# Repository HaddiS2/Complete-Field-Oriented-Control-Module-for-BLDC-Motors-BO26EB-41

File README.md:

# Complete-Field-Oriented-Control-Module-for-BLDC-Motors-BO26EB-41
Custom field-oriented control (FOC) motor controller with USB-C Power Delivery.

This repository contains the hardware design files, firmware, and test rig for a custom brushless motor controller built around field-oriented control (FOC). The board negotiates its supply voltage over USB-C Power Delivery using an STUSB4500, and measures rotor position with a TLE5009 magnetic encoder mounted directly beneath the motor shaft. The PCB was designed in KiCad, and a custom test rig — modeled in Fusion 360 and 3D printed — holds the motor and controller in fixed alignment to keep the encoder-to-magnet spacing constant for repeatable position- and velocity-control testing.

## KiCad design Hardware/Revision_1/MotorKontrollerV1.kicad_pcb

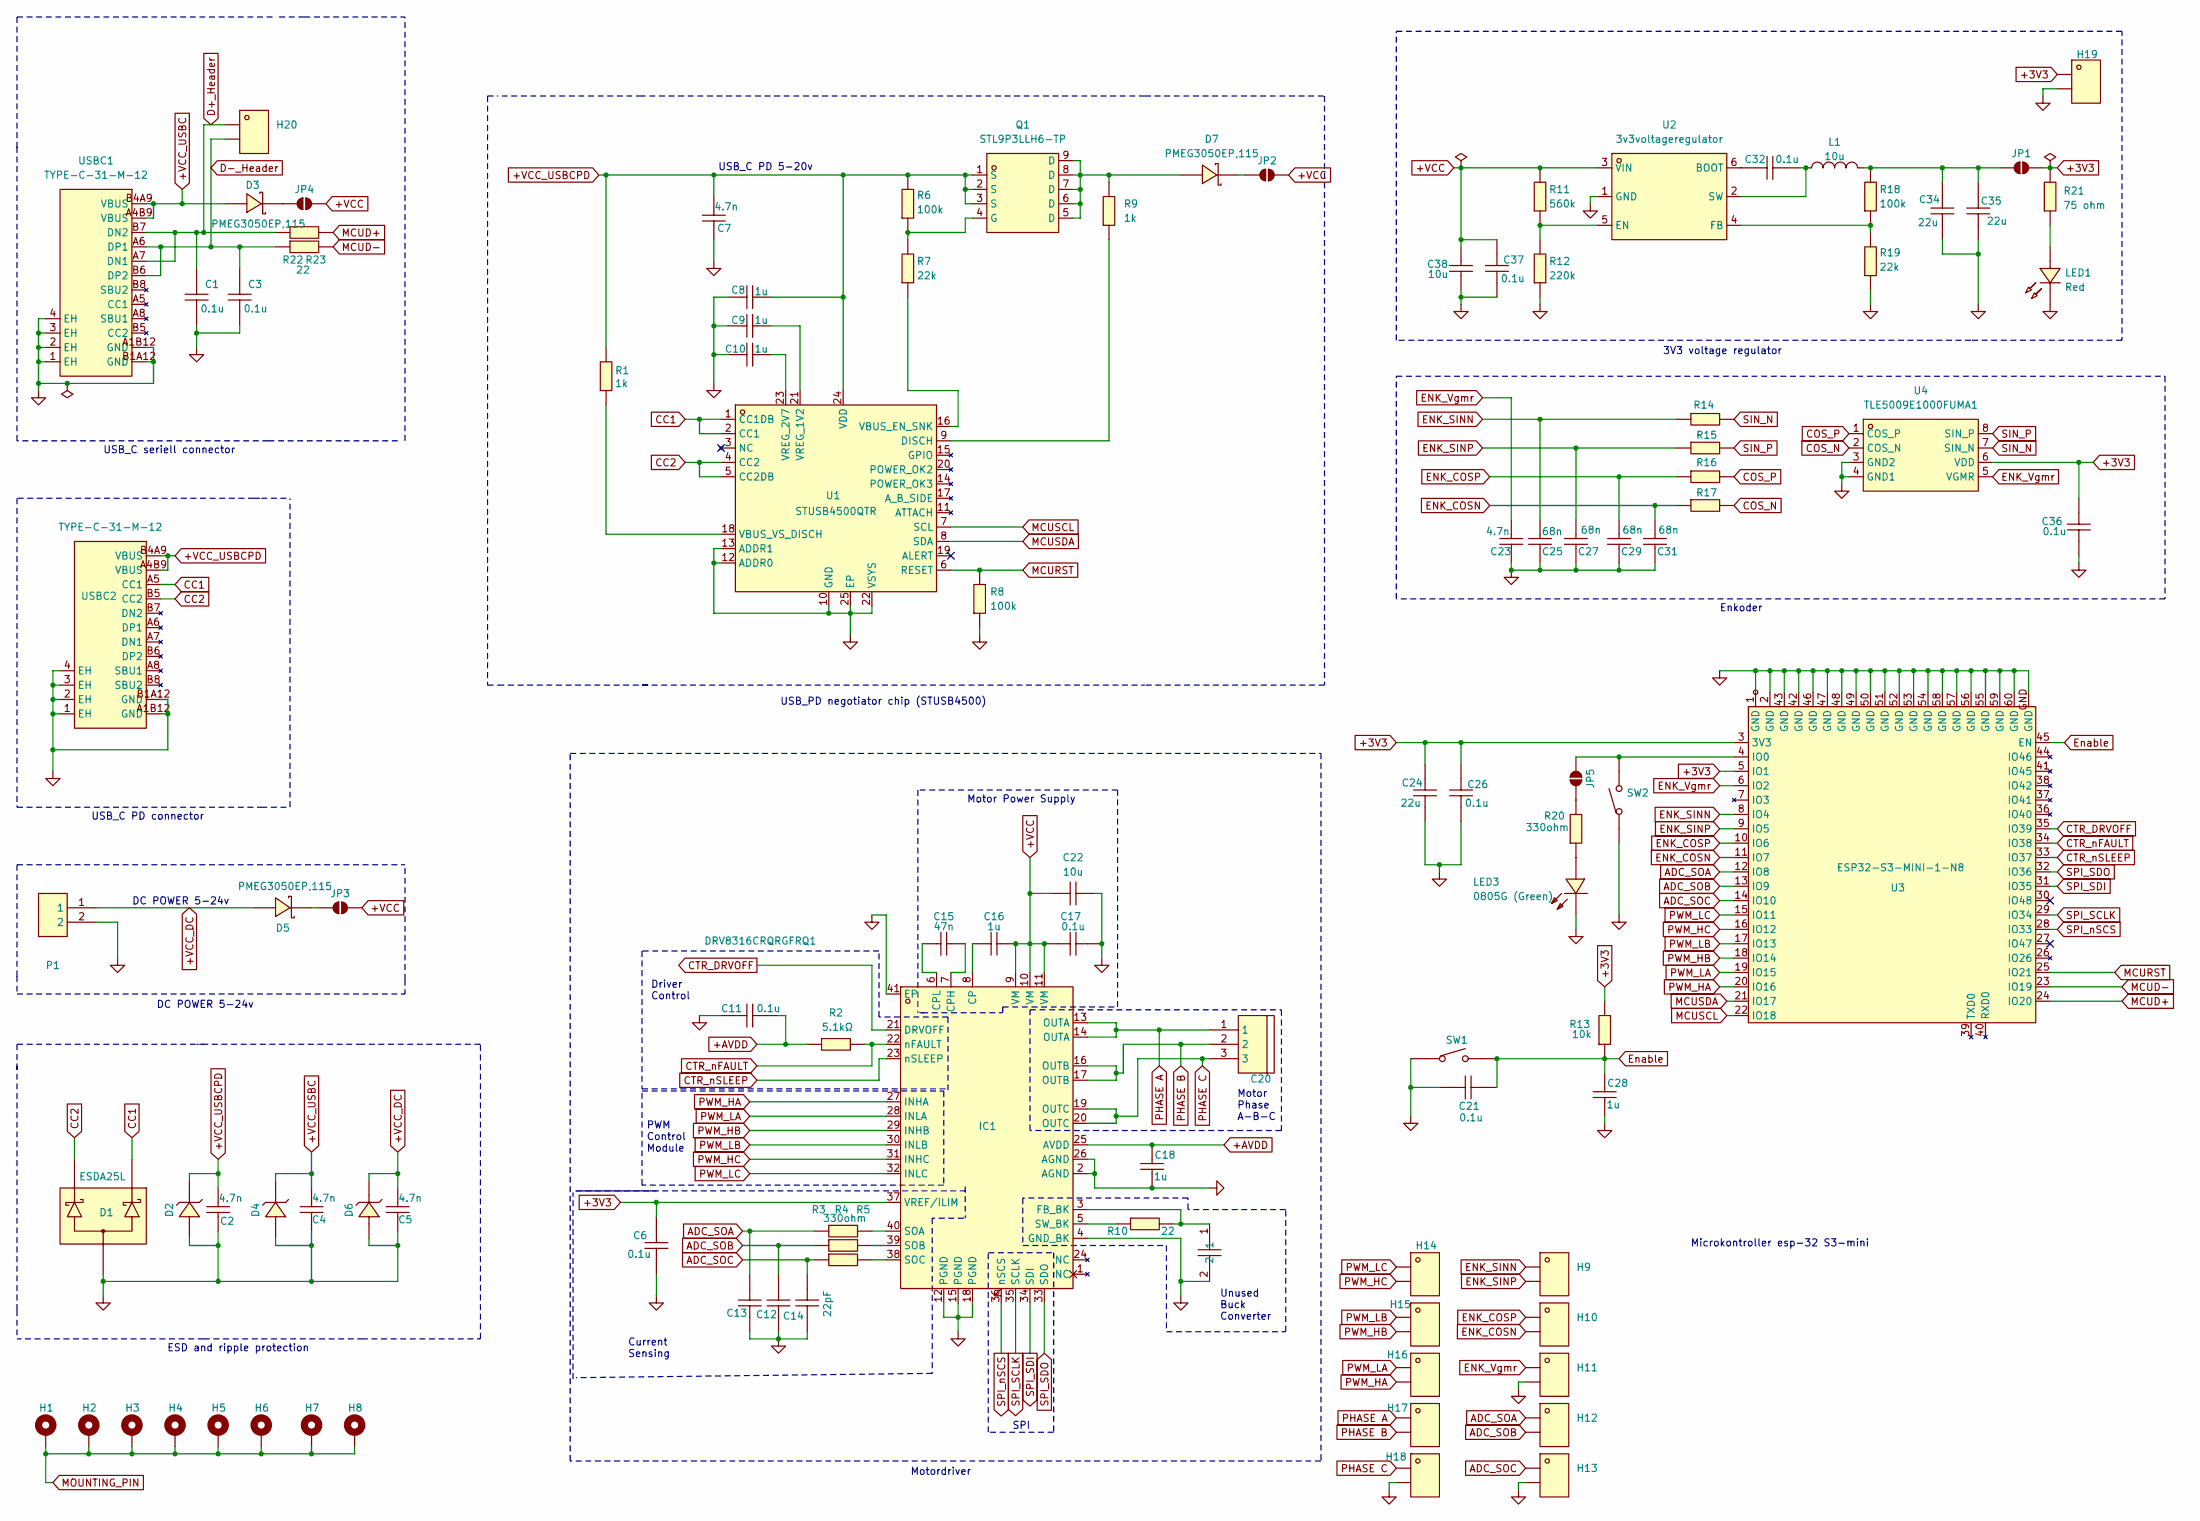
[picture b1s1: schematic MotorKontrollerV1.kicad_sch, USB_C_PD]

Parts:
C1, C3, C6, C11, C17, C21, C26, C32, C36, C37: 0.1u; C0603; LCSC Part C14663
C2, C4, C5, C7, C23: 4.7n; C0603; LCSC Part C53987
C8, C9, C10, C16, C18, C28: 1u; C0805; LCSC Part C28323
C12, C13, C14: 22pF; C0402; LCSC Part C1555
C15: 47n; C0603; LCSC Part C1622
C19, C24, C34, C35: 22u; C0805; LCSC Part C45783
C20: WJ500V-5.08-3P-14-00A; CONN-TH_3P-P5.00_WJ500V-5.08-3P; LCSC Part C72334
C22, C38: 10u; C1206; LCSC Part C13585
C25, C27, C29, C31: 68n; C1206; LCSC Part C77084
D1: ESDA25L; SOT-23-3_L2.9-W1.3-P1.90-LS2.4-BR; LCSC Part C95343
D2, D4, D6: ESDA25P35-1U1M_C19829649; DFN1610-2L_L1.6-W1.0-P1.10-RD; LCSC Part C19829649
D3, D5, D7: PMEG3050EP,115; SOD-128_L3.7-W2.5-LS4.7-RD; LCSC Part C50603
H1, H2, H3, H4, H5, H6, H7, H8: MountingHole_Pad_MP; MountingHole_3.2mm_M3_Pad_Via
H9, H10, H11, H12, H13, H14, H15, H16, H17, H18, H19, H20: PZ254V-11-02P; HDR-TH_2P-P2.54-V-M; LCSC Part C492401
IC1: DRV8316CRQRGFRQ1; VQFN-40_L7.0-W5.0-P0.50-BL-EP5.7; LCSC Part C20345369
JP1, JP2, JP3, JP4, JP5: SolderJumper_2_Open; SolderJumper-2_P1.3mm_Open_RoundedPad1.0x1.5mm
L1: 10u; IND-SMD_L3.2-W2.5_CKST322512-2.2UH; LCSC Part C39846661
LED1: Red; LED0603-RD_RED; LCSC Part C2286
LED3: 0805G (Green); LED0805-R-RD; LCSC Part C2297
P1: WJ500V-5.08-2P-14-00A; CONN-TH_2P-P5.00_WJ500V-5.08-2P; LCSC Part C8465
Q1: STL9P3LLH6-TP; DFN-8_L3.0-W3.0-P0.65-BL_WPM3028-8; LCSC Part C49452333
R1, R9: 1k; R0805; LCSC Part C17513
R2: 5.1kΩ; R0402; LCSC Part C25905
R3, R4, R5, R20: 330ohm; R0805; LCSC Part C17630
R6, R8, R18: 100k; R0805_NEW; LCSC Part C149504
R7, R19: 22k; R0805; LCSC Part C17560
R10, R22, R23: 22; R0805; LCSC Part C17561
R11: 560k; R0805; LCSC Part C15785
R12: 220k; R0805; LCSC Part C17556
R13, R14, R15, R16, R17: 10k; R0603; LCSC Part C25804
R21: 75 ohm; R0603; LCSC Part C4275
SW1, SW2: TS-1088-AR02016; SW-SMD_L3.9-W3.0-P4.45; LCSC Part C720477
U1: STUSB4500QTR; QFN-24_L4.0-W4.0-P0.50-BL-EP2.8; LCSC Part C2678061
U2: 3v3voltageregulator; SOT-23-6_L2.9-W1.6-P0.95-LS2.8-BL; LCSC Part C191884
U3: ESP32-S3-MINI-1-N8; BULETM-SMD_ESP32-S3-MINI-1-N8; LCSC Part C2913206
U4: TLE5009E1000FUMA1; PG-DSO-8_L5.0-W4.0-P1.27-LS6.0-BL; LCSC Part C2655191
USBC1, USBC2: TYPE-C-31-M-12; USB-C_SMD-TYPE-C-31-M-12_1; LCSC Part C165948

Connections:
+3V3: C6.1, C24.1, C26.2, C36.2, H19.1, IC1.37 (VREF/ILIM), JP1.2 (B), R13.2, R21.2, U3.3 (3V3), U3.5 (IO1), U4.6 (VDD)
+AVDD: C11.2, C18.2, IC1.25 (AVDD), R2.1
+VCC: C16.1, C17.1, C22.1, C37.2, C38.2, IC1.9 (VM), IC1.10 (VM), IC1.11 (VM), JP2.2 (B), JP3.2 (B), JP4.2 (B), R11.2, U2.3 (VIN)
+VCC_DC: C5.2, D5.2 (A), D6.1 (C), P1.1
+VCC_USBC: C4.2, D3.2 (A), D4.1 (C), USBC1.A4B9 (VBUS), USBC1.B4A9 (VBUS)
+VCC_USBCPD: C2.2, C7.2, C8.1, D2.1 (C), Q1.1 (S), Q1.2 (S), Q1.3 (S), R1.2, R6.2, U1.24 (VDD), USBC2.A4B9 (VBUS), USBC2.B4A9 (VBUS)
ADC_SOA: C12.2, H12.1, R3.1, U3.12 (IO8)
ADC_SOB: C13.2, H12.2, R4.1, U3.13 (IO9)
ADC_SOC: C14.2, H13.1, R5.1, U3.14 (IO10)
CC1: D1.1, U1.1 (CC1DB), U1.2 (CC1), USBC2.A5 (CC1)
CC2: D1.2, U1.4 (CC2), U1.5 (CC2DB), USBC2.B5 (CC2)
COS_N: R17.2, U4.2 (COS_N)
COS_P: R16.2, U4.1 (COS_P)
CTR_DRVOFF: IC1.21 (DRVOFF), U3.35 (IO39)
CTR_nFAULT: IC1.22 (nFAULT), R2.2, U3.34 (IO38)
CTR_nSLEEP: IC1.23 (nSLEEP), U3.33 (IO37)
D+_Header: C1.1, H20.1, R22.1, USBC1.A7 (DN1), USBC1.B7 (DN2)
D-_Header: C3.1, H20.2, R23.1, USBC1.A6 (DP1), USBC1.B6 (DP2)
ENK_COSN: C31.2, H10.2, R17.1, U3.11 (IO7)
ENK_COSP: C29.2, H10.1, R16.1, U3.10 (IO6)
ENK_SINN: C25.2, H9.1, R14.1, U3.8 (IO4)
ENK_SINP: C27.2, H9.2, R15.1, U3.9 (IO5)
ENK_Vgmr: C23.2, H11.1, U3.6 (IO2), U4.5 (VGMR)
Enable: C21.1, C28.2, R13.1, SW1.2, U3.45 (EN)
GND: C1.2, C2.1, C3.2, C4.1, C5.1, C6.2, C7.1, C8.2, C9.2, C10.2, C11.1, C12.1, C13.1, C14.1, C17.2, C18.1, C19.2, C21.2, C22.2, C23.1, C24.2, C25.1, C26.1, C27.1, C28.1, C29.1, C31.1, C34.2, C35.2, C36.1, C37.1, C38.1, D1.3, D2.2 (A), D4.2 (A), D6.2 (A), H11.2, H13.2, H18.2, H19.2, IC1.2 (AGND), IC1.4 (GND_BK), IC1.12 (PGND), IC1.15 (PGND), IC1.18 (PGND), IC1.26 (AGND), IC1.41 (EP), LED1.1 (K), LED3.2 (K), P1.2, R8.1, R12.1, R19.1, SW1.1, SW2.1, U1.10 (GND), U1.12 (ADDR0), U1.13 (ADDR1), U1.22 (VSYS), U1.25 (EP), U2.1 (GND), U3.1 (GND), U3.2 (GND), U3.42 (GND), U3.43 (GND), U3.46 (GND), U3.47 (GND), U3.48 (GND), U3.49 (GND), U3.50 (GND), U3.51 (GND), U3.52 (GND), U3.53 (GND), U3.54 (GND), U3.55 (GND), U3.56 (GND), U3.57 (GND), U3.58 (GND), U3.59 (GND), U3.60 (GND), U3.GND, U4.3 (GND2), U4.4 (GND1), USBC1.1 (EH), USBC1.2 (EH), USBC1.3 (EH), USBC1.4 (EH), USBC1.A1B12 (GND), USBC1.B1A12 (GND), USBC2.1 (EH), USBC2.2 (EH), USBC2.3 (EH), USBC2.4 (EH), USBC2.A1B12 (GND), USBC2.B1A12 (GND)
MCUD+: R22.2, U3.24 (IO20)
MCUD-: R23.2, U3.23 (IO19)
MCURST: R8.2, U1.6 (RESET), U3.25 (IO21)
MCUSCL: U1.7 (SCL), U3.22 (IO18)
MCUSDA: U1.8 (SDA), U3.21 (IO17)
MOUNTING_PIN: H1.1 (MP), H2.1 (MP), H3.1 (MP), H4.1 (MP), H5.1 (MP), H6.1 (MP), H7.1 (MP), H8.1 (MP)
unnamed: D3.1 (K), JP4.1 (A)
unnamed: D5.1 (K), JP3.1 (A)
unnamed: D7.2 (A), Q1.5 (D), Q1.6 (D), Q1.7 (D), Q1.8 (D), Q1.9 (D), R9.2
unnamed: D7.1 (K), JP2.1 (A)
unnamed: C16.2, IC1.8 (CP)
unnamed: C15.2, IC1.7 (CPH)
unnamed: C15.1, IC1.6 (CPL)
unnamed: C19.1, IC1.3 (FB_BK), R10.2
unnamed: IC1.40 (SOA), R3.2
unnamed: IC1.39 (SOB), R4.2
unnamed: IC1.38 (SOC), R5.2
unnamed: IC1.5 (SW_BK), R10.1
unnamed: C34.1, C35.1, JP1.1 (A), L1.2, R18.2
unnamed: JP5.1 (A), SW2.2, U3.4 (IO0)
unnamed: JP5.2 (B), R20.2
unnamed: LED1.2 (A), R21.1
unnamed: LED3.1 (A), R20.1
unnamed: Q1.4 (G), R6.1, R7.2
unnamed: R9.1, U1.9 (DISCH)
unnamed: R7.1, U1.16 (VBUS_EN_SNK)
unnamed: R1.1, U1.18 (VBUS_VS_DISCH)
unnamed: C9.1, U1.21 (VREG_1V2)
unnamed: C10.1, U1.23 (VREG_2V7)
unnamed: C32.2, U2.6 (BOOT)
unnamed: R11.1, R12.2, U2.5 (EN)
unnamed: R18.1, R19.2, U2.4 (FB)
unnamed: C32.1, L1.1, U2.2 (SW)
PHASE A: C20.1, H17.1, IC1.13 (OUTA), IC1.14 (OUTA)
PHASE B: C20.2, H17.2, IC1.16 (OUTB), IC1.17 (OUTB)
PHASE C: C20.3, H18.1, IC1.19 (OUTC), IC1.20 (OUTC)
PWM_HA: H16.2, IC1.27 (INHA), U3.20 (IO16)
PWM_HB: H15.2, IC1.29 (INHB), U3.18 (IO14)
PWM_HC: H14.2, IC1.31 (INHC), U3.16 (IO12)
PWM_LA: H16.1, IC1.28 (INLA), U3.19 (IO15)
PWM_LB: H15.1, IC1.30 (INLB), U3.17 (IO13)
PWM_LC: H14.1, IC1.32 (INLC), U3.15 (IO11)
SIN_N: R14.2, U4.7 (SIN_N)
SIN_P: R15.2, U4.8 (SIN_P)
SPI_SCLK: IC1.35 (SCLK), U3.29 (IO34)
SPI_SDI: IC1.34 (SDI), U3.31 (IO35)
SPI_SDO: IC1.33 (SDO), U3.32 (IO36)
SPI_nSCS: IC1.36 (nSCS), U3.28 (IO33)

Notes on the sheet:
Motor Power Supply
Motor Phase A-B-C
Driver Control
USB_C PD 5-20v
PWM Control Module
SPI
Current Sensing
3V3 voltage regulator
Microkontroller esp-32 S3-mini
USB_C PD connector
DC POWER 5-24v
USB_C seriell connector
Unused Buck Converter
Enkoder
Motordriver
ESD and ripple protection
USB_PD negotiator chip (STUSB4500)

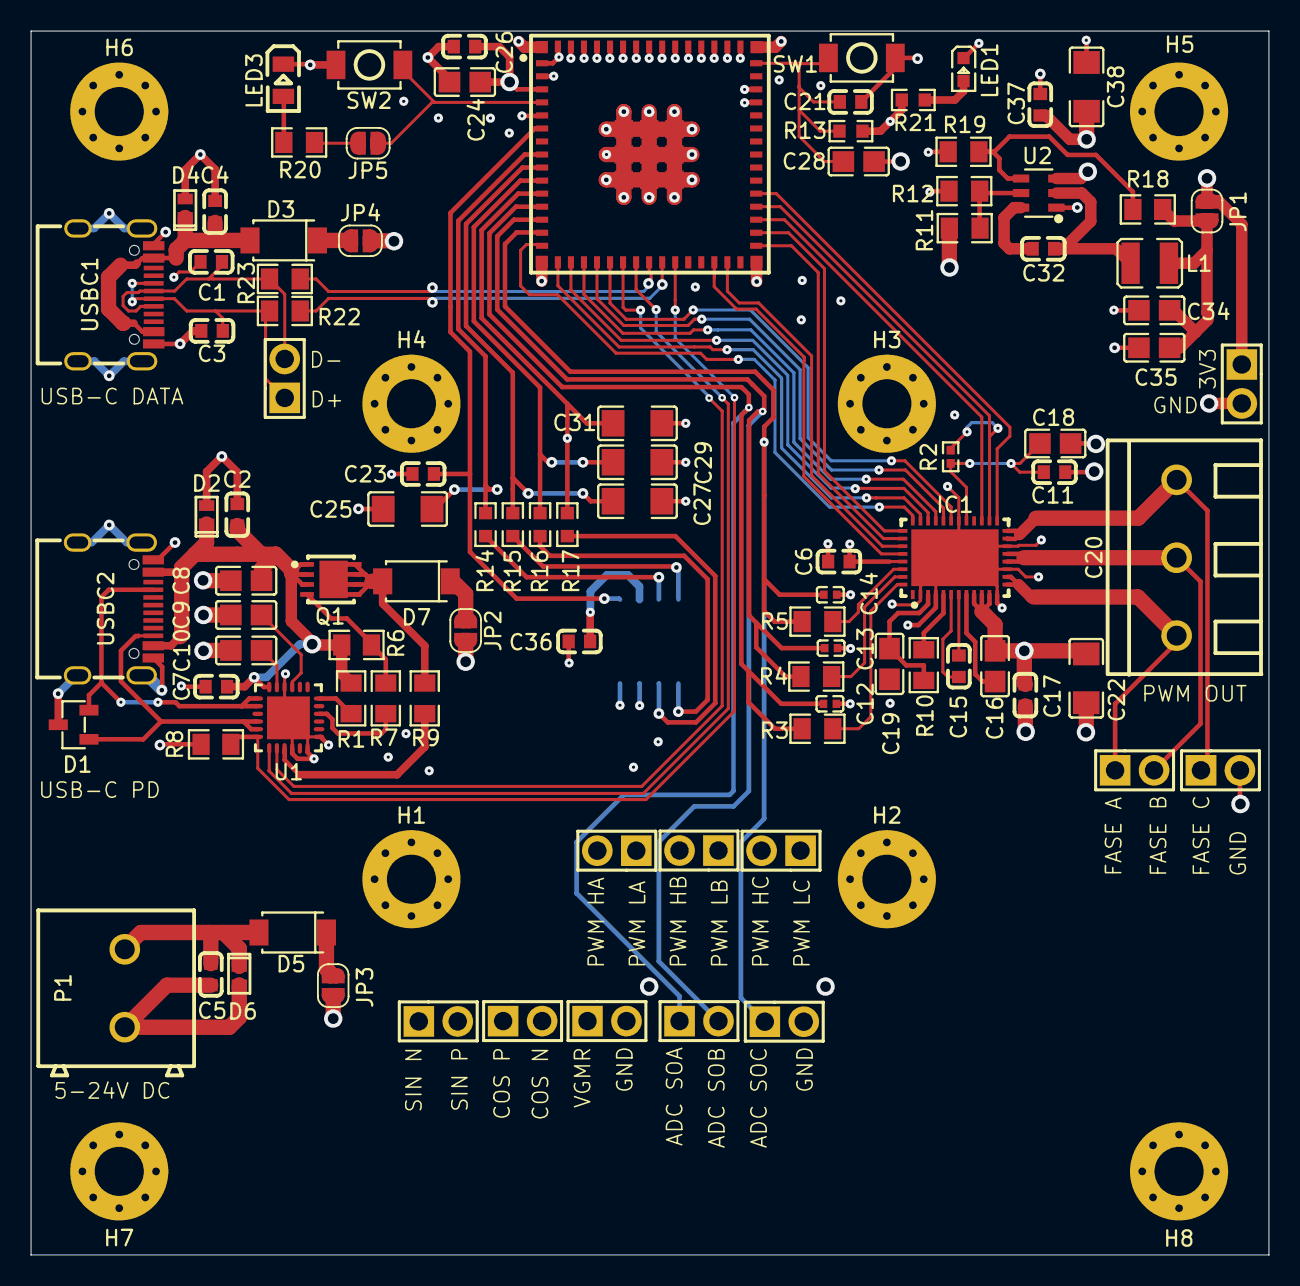
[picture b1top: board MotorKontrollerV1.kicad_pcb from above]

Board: 6 copper layers, 80.7 x 79.8 mm, 105 parts (1 on the bottom side), 73 nets.

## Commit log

2026-05-19 Expand README with project details and hardware info
    Added detailed project description including hardware and firmware information.
2026-05-19 Legg til USB_PD_Test.ino
2026-05-19 Legg til BLDC_FOC_Driver og USB_PD_Test prosjekt
2026-05-19 Fjern placeholder.txt
2026-05-19 Legg til README-filer med installasjonsinstruksjonar
2026-05-19 Update README files to English
2026-05-19 Legg til Fusion360 CAD-filer (.f3z)
2026-05-19 Add component list (PDF and Excel)
2026-05-19 Add Hardware Folder
2026-05-19 Add PNG images to CAD folder
2026-05-19 Added hardware-files for revision1 and revision2 of the board
2026-05-19 Added Pinout File
2026-05-19 Added Pinout file and removed placeholder.txt files from Hardware
2026-05-19 Added PDF of the schematic
2026-05-19 Added the 3d models of the PCB
